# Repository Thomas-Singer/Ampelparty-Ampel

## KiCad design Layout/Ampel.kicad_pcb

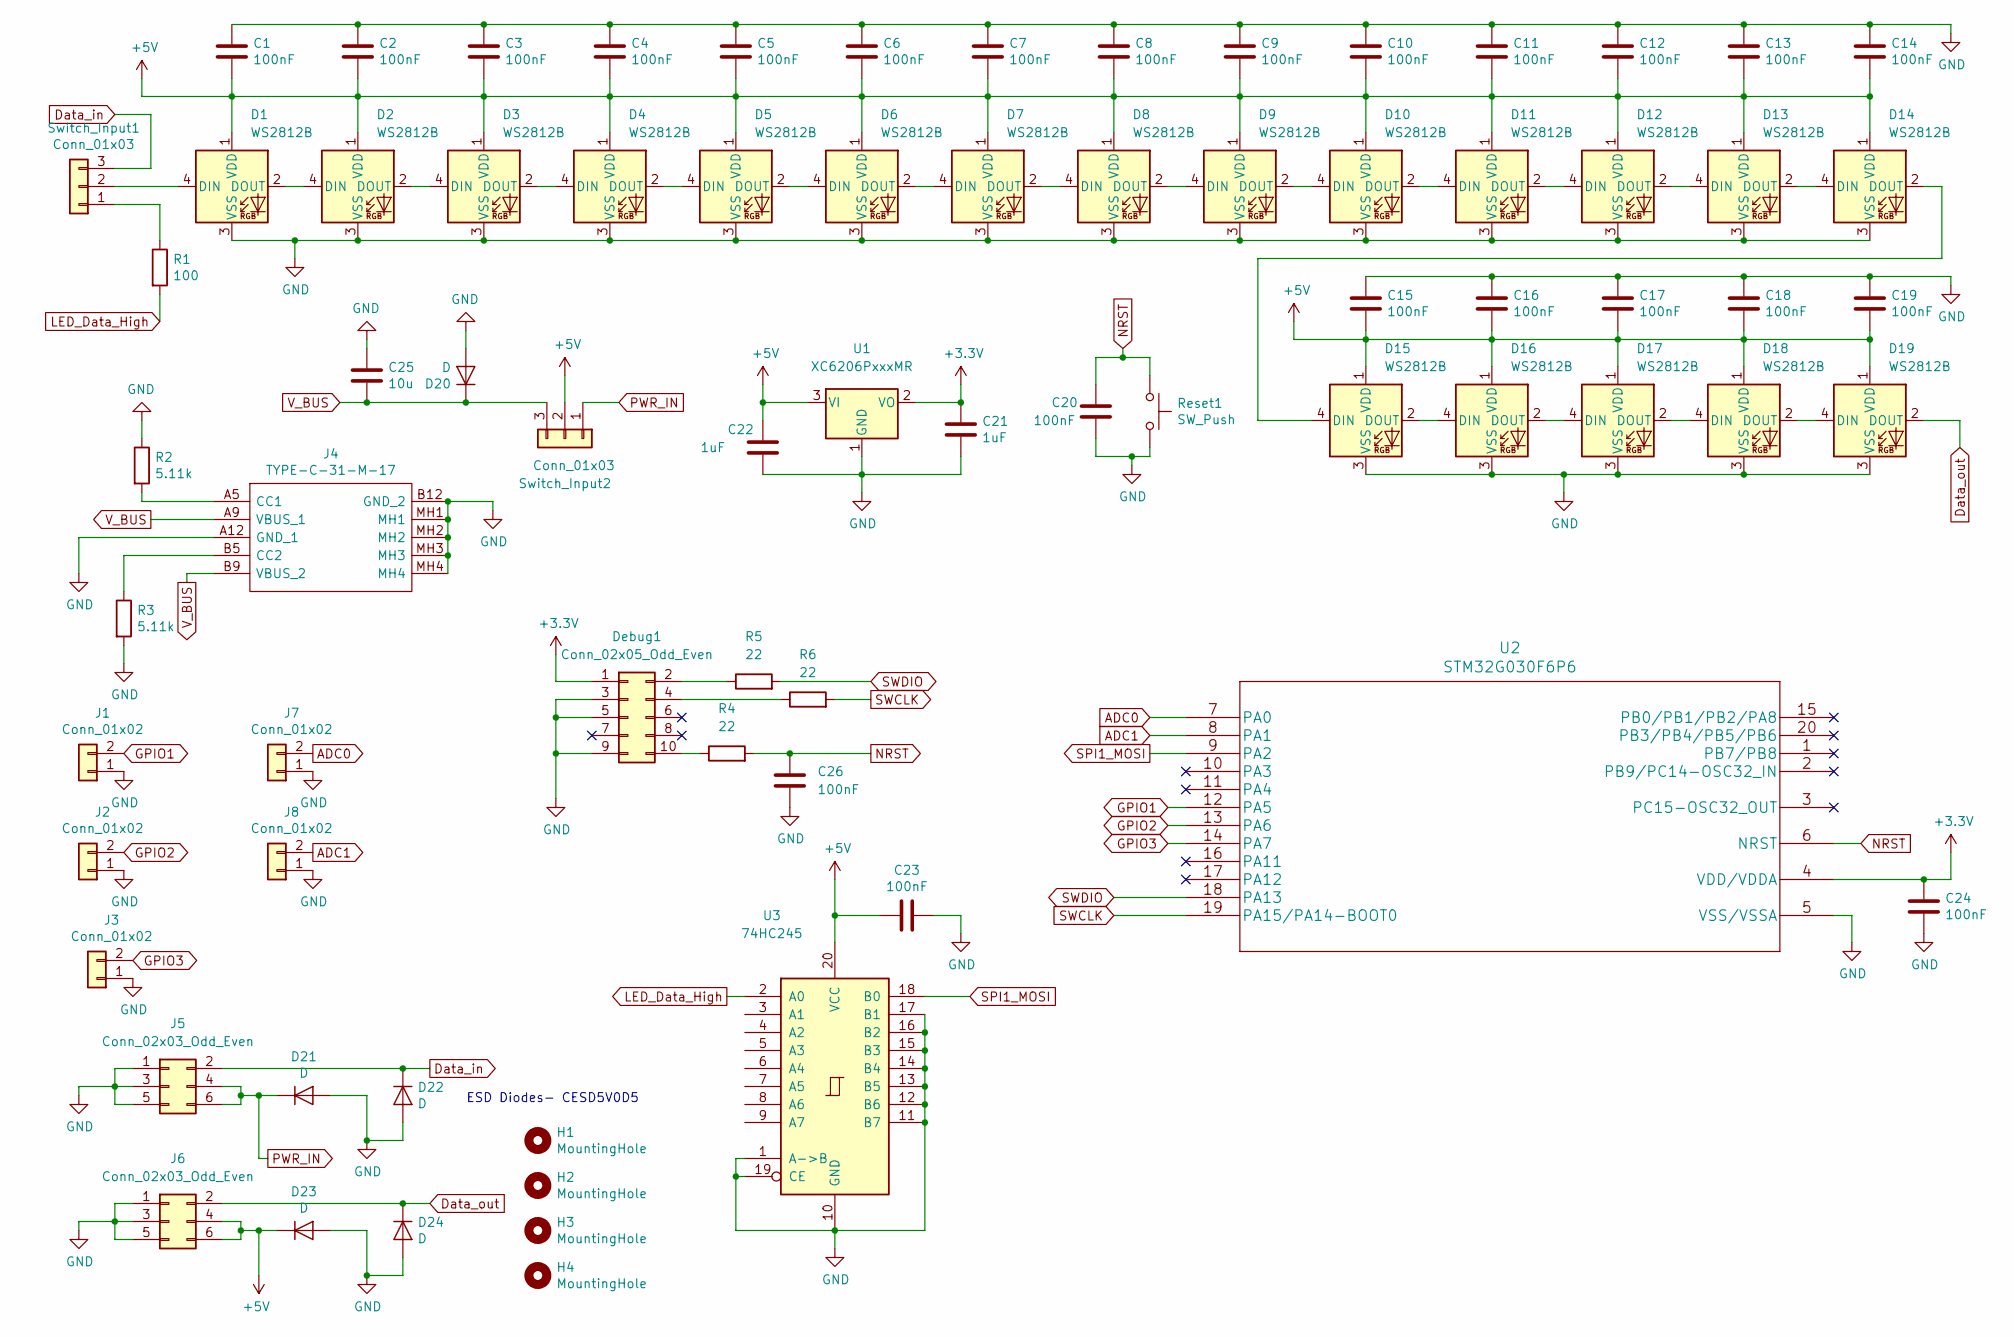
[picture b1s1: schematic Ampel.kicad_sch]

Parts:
C1, C2, C3, C4, C5, C6, C7, C8, C9, C10, C11, C12, C13, C14, C15, C16, C17, C18, C19, C20, C23, C24, C26: 100nF; C_0603_1608Metric
C21, C22: 1uF; C_0805_2012Metric
C25: 10u; C_1210_3225Metric
D1, D2, D3, D4, D5, D6, D7, D8, D9, D10, D11, D12, D13, D14, D15, D16, D17, D18, D19: WS2812B; LED_WS2812B_PLCC4_5.0x5.0mm_P3.2mm
D20, D21, D22, D23, D24: D; D_SOD-523
Debug1: Conn_02x05_Odd_Even; IDC-Header_2x05_P2.54mm_Vertical
H1, H2, H3, H4: MountingHole; MountingHole_3.5mm_Pad
J1, J2, J3, J7, J8: Conn_01x02; PinHeader_1x02_P2.54mm_Vertical
J4: TYPE-C-31-M-17; TYPEC31M17; Manufacturer_Part_Number TYPE-C-31-M-17
J5, J6: Conn_02x03_Odd_Even; IDC-Header_2x03_P2.54mm_Vertical
R1: 100; R_0603_1608Metric
R2, R3: 5.11k; R_0603_1608Metric
R4, R5, R6: 22; R_0603_1608Metric
Reset1: SW_Push; SW_SPST_EVPBF
Switch_Input1, Switch_Input2: Conn_01x03; PinHeader_1x03_P2.54mm_Vertical
U1: XC6206PxxxMR; SOT-23
U2: STM32G030F6P6; TSSOP-20_4.4x6.5mm_P0.65mm
U3: 74HC245; SSOP-20_5.3x7.2mm_P0.65mm

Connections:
+3V3: C21.1, C24.1, Debug1.1, U1.2 (VO), U2.4 (VDD/VDDA)
+5V: C1.1, C2.1, C3.1, C4.1, C5.1, C6.1, C7.1, C8.1, C9.1, C10.1, C11.1, C12.1, C13.1, C14.1, C15.1, C16.1, C17.1, C18.1, C19.1, C22.2, C23.2, D1.1 (VDD), D2.1 (VDD), D3.1 (VDD), D4.1 (VDD), D5.1 (VDD), D6.1 (VDD), D7.1 (VDD), D8.1 (VDD), D9.1 (VDD), D10.1 (VDD), D11.1 (VDD), D12.1 (VDD), D13.1 (VDD), D14.1 (VDD), D15.1 (VDD), D16.1 (VDD), D17.1 (VDD), D18.1 (VDD), D19.1 (VDD), D23.1 (K), J6.4, J6.6, Switch_Input2.2, U1.3 (VI), U3.20 (VCC)
ADC0: J7.2, U2.7 (PA0); also elsewhere on the board
ADC1: J8.2, U2.8 (PA1); also elsewhere on the board
Data_in: D22.1 (K), J5.2, Switch_Input1.3
Data_out: D19.2 (DOUT), D24.1 (K), J6.2
GND: C1.2, C2.2, C3.2, C4.2, C5.2, C6.2, C7.2, C8.2, C9.2, C10.2, C11.2, C12.2, C13.2, C14.2, C15.2, C16.2, C17.2, C18.2, C19.2, C20.2, C21.2, C22.1, C23.1, C24.2, C25.1, C26.2, D1.3 (VSS), D2.3 (VSS), D3.3 (VSS), D4.3 (VSS), D5.3 (VSS), D6.3 (VSS), D7.3 (VSS), D8.3 (VSS), D9.3 (VSS), D10.3 (VSS), D11.3 (VSS), D12.3 (VSS), D13.3 (VSS), D14.3 (VSS), D15.3 (VSS), D16.3 (VSS), D17.3 (VSS), D18.3 (VSS), D19.3 (VSS), D20.2 (A), D21.2 (A), D22.2 (A), D23.2 (A), D24.2 (A), Debug1.3, Debug1.5, Debug1.9, J1.1, J2.1, J3.1, J4.A12 (GND_1), J4.B12 (GND_2), J4.MH1, J4.MH2, J4.MH3, J4.MH4, J5.1, J5.3, J5.5, J6.1, J6.3, J6.5, J7.1, J8.1, R2.1, R3.2, Reset1.2, U1.1 (GND), U2.5 (VSS/VSSA), U3.1 (A->B), U3.10 (GND), U3.11 (B7), U3.12 (B6), U3.13 (B5), U3.14 (B4), U3.15 (B3), U3.16 (B2), U3.17 (B1), U3.19 (CE); also elsewhere on the board
GPIO1: J1.2, U2.12 (PA5); also elsewhere on the board
GPIO2: J2.2, U2.13 (PA6); also elsewhere on the board
GPIO3: J3.2, U2.14 (PA7); also elsewhere on the board
LED_Data_High: R1.2, U3.2 (A0)
NRST: C20.1, C26.1, R4.2, Reset1.1, U2.6 (NRST)
unnamed: D1.2 (DOUT), D2.4 (DIN)
unnamed: D1.4 (DIN), Switch_Input1.2
unnamed: D2.2 (DOUT), D3.4 (DIN)
unnamed: D3.2 (DOUT), D4.4 (DIN)
unnamed: D4.2 (DOUT), D5.4 (DIN)
unnamed: D5.2 (DOUT), D6.4 (DIN)
unnamed: D6.2 (DOUT), D7.4 (DIN)
unnamed: D7.2 (DOUT), D8.4 (DIN)
unnamed: D8.2 (DOUT), D9.4 (DIN)
unnamed: D10.2 (DOUT), D11.4 (DIN)
unnamed: D9.2 (DOUT), D10.4 (DIN)
unnamed: D11.2 (DOUT), D12.4 (DIN)
unnamed: D12.2 (DOUT), D13.4 (DIN)
unnamed: D13.2 (DOUT), D14.4 (DIN)
unnamed: D14.2 (DOUT), D15.4 (DIN)
unnamed: D15.2 (DOUT), D16.4 (DIN)
unnamed: D16.2 (DOUT), D17.4 (DIN)
unnamed: D17.2 (DOUT), D18.4 (DIN)
unnamed: D18.2 (DOUT), D19.4 (DIN)
unnamed: Debug1.2, R5.1
unnamed: Debug1.4, R6.1
unnamed: Debug1.10, R4.1
unnamed: J4.A5 (CC1), R2.2
unnamed: J4.B5 (CC2), R3.1
unnamed: R1.1, Switch_Input1.1
PWR_IN: D21.1 (K), J5.4, J5.6, Switch_Input2.1
SPI1_MOSI: U2.9 (PA2), U3.18 (B0)
SWCLK: R6.2, U2.19 (PA15/PA14-BOOT0)
SWDIO: R5.2, U2.18 (PA13)
V_BUS: C25.2, D20.1 (K), J4.A9 (VBUS_1), J4.B9 (VBUS_2), Switch_Input2.3

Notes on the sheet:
ESD Diodes- CESD5V0D5

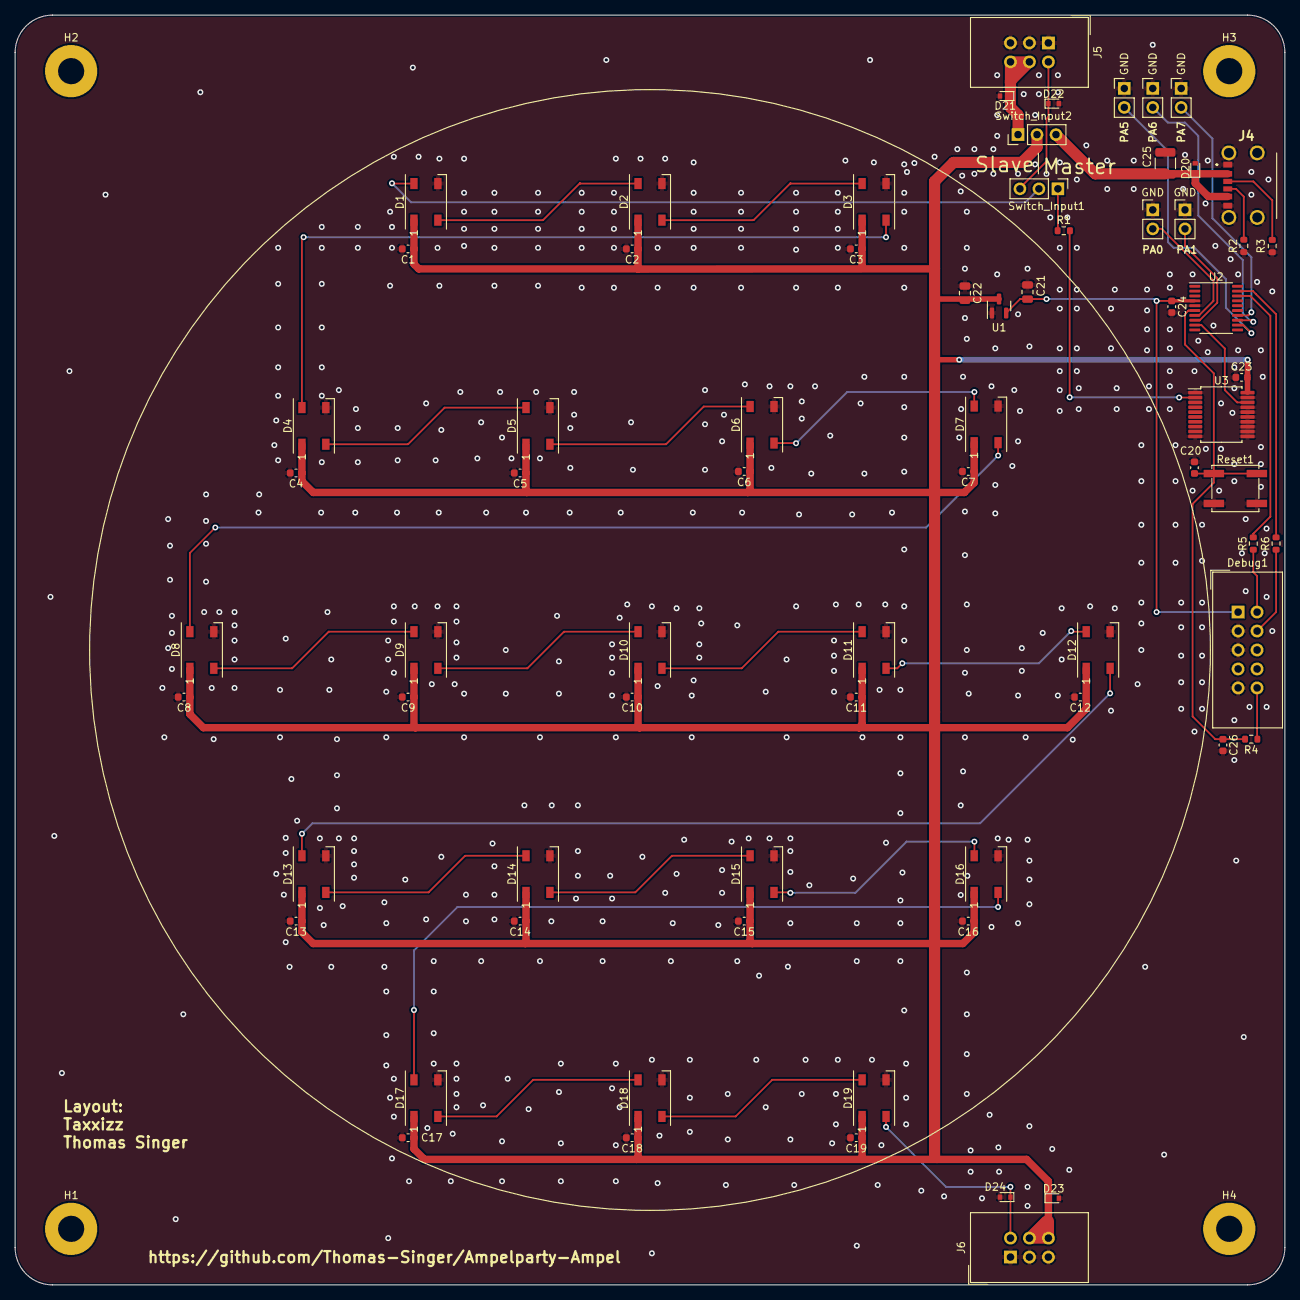
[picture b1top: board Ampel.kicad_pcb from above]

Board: 2 copper layers, 170.0 x 170.0 mm, 75 parts (0 on the bottom side), 42 nets.

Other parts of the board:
GND: Conn_01x02; PinHeader_1x02_P2.54mm_Vertical
GND#2, GND#3, GND#4, GND#5: Conn_01x02; PinHeader_1x02_P2.54mm_Vertical

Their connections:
ADC0: GND#4.2; also elsewhere on the board
ADC1: GND#5.2; also elsewhere on the board
GND: GND.1, GND#2.1, GND#3.1, GND#4.1, GND#5.1; also elsewhere on the board
GPIO1: GND.2; also elsewhere on the board
GPIO2: GND#2.2; also elsewhere on the board
GPIO3: GND#3.2; also elsewhere on the board

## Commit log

2022-09-18 Final Layout
2022-09-18 Initial SW Project
2022-10-12 Added WS2812b-IF, currently not working
2022-10-13 test
2022-10-17 control works now the NSSP mode of the SPI was the reason. So the clock waites sometimes which destroys the timing.
